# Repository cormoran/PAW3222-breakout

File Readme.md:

# PAW3222-LU breakout board

I've never assembled it. I don't know whether it works or not!

動作未確認！

**Drill hole size is slightly smaller than lens's bump. You should change it to slightly larger.**

- height 9mm
- width 14.8mm
- 6pin 0.5mm pitch FFC
- 6pin 1.27mm pitch hole for testing
- Designed for 1 layer PCB assembly

How it was designed -> https://x.com/cormoran707/status/1889661277347193108

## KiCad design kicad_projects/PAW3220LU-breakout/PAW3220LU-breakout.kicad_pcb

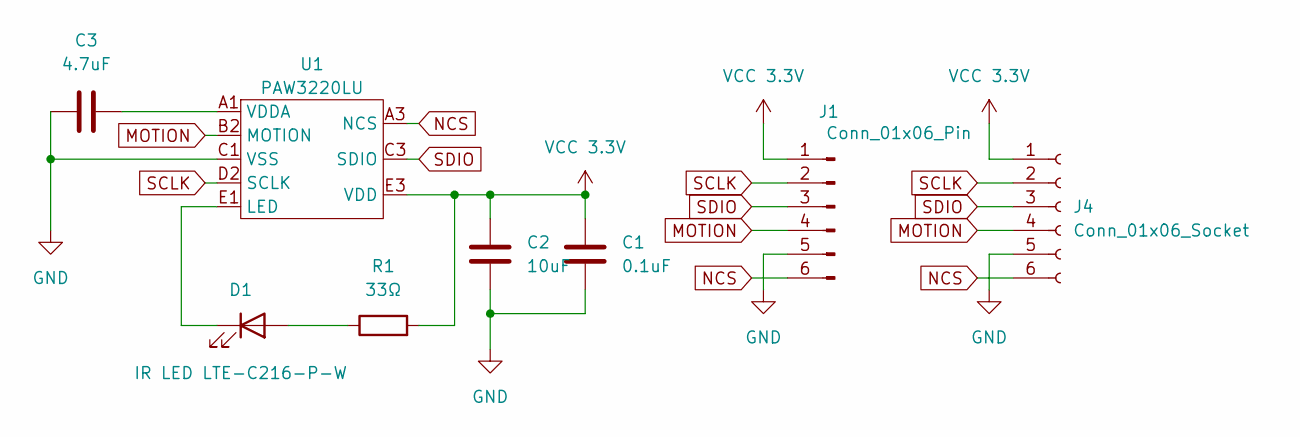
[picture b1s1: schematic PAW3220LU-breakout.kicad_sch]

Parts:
C1: 0.1uF; C_0201_0603Metric; LCSC C14663
C2: 10uF; C_0201_0603Metric; LCSC C19702
C3: 4.7uF; C_0201_0603Metric; LCSC C19666
D1: IR LED LTE-C216-P-W; LTE-C216-P-W; LCSC C2942980
J1: Conn_01x06_Pin; Jushuo_AFC07-S06FCA-00_1x6-1MP_P0.50_Horizontal; LCSC C262553
J4: Conn_01x06_Socket; PinHeader_1x06_P1.27mm_Vertical
R1: 33Ω; R_0201_0603Metric; LCSC C23140
U1: PAW3220LU; PAW3222LU; LCSC C9900022540

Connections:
GND: C1.2, C2.2, C3.2, J1.5, J4.5, U1.C1 (VSS)
MOTION: J1.4, J4.4, U1.B2 (MOTION)
NCS: J1.6, J4.6, U1.A3 (NCS)
unnamed: D1.2 (A), R1.1
unnamed: D1.1 (K), U1.E1 (LED)
unnamed: C3.1, U1.A1 (VDDA)
SCLK: J1.2, J4.2, U1.D2 (SCLK)
SDIO: J1.3, J4.3, U1.C3 (SDIO)
VCC 3.3V: C1.1, C2.1, J1.1, J4.1, R1.2, U1.E3 (VDD)

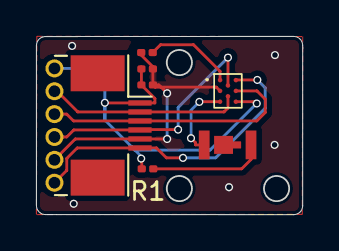
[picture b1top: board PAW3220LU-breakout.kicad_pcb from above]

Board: 2 copper layers, 14.7 x 9.9 mm, 8 parts (0 on the bottom side), 9 nets.

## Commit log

2025-01-23 Import PAW3220LU-breakout from private repo
2025-01-23 Add image and readme
2025-01-23 Add figure and LICENSE
2025-02-12 Add warning and pcb picture

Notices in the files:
kicad_projects/PAW3220LU-breakout/PAW3220LU-breakout.kicad_pcb:
©cormoran
